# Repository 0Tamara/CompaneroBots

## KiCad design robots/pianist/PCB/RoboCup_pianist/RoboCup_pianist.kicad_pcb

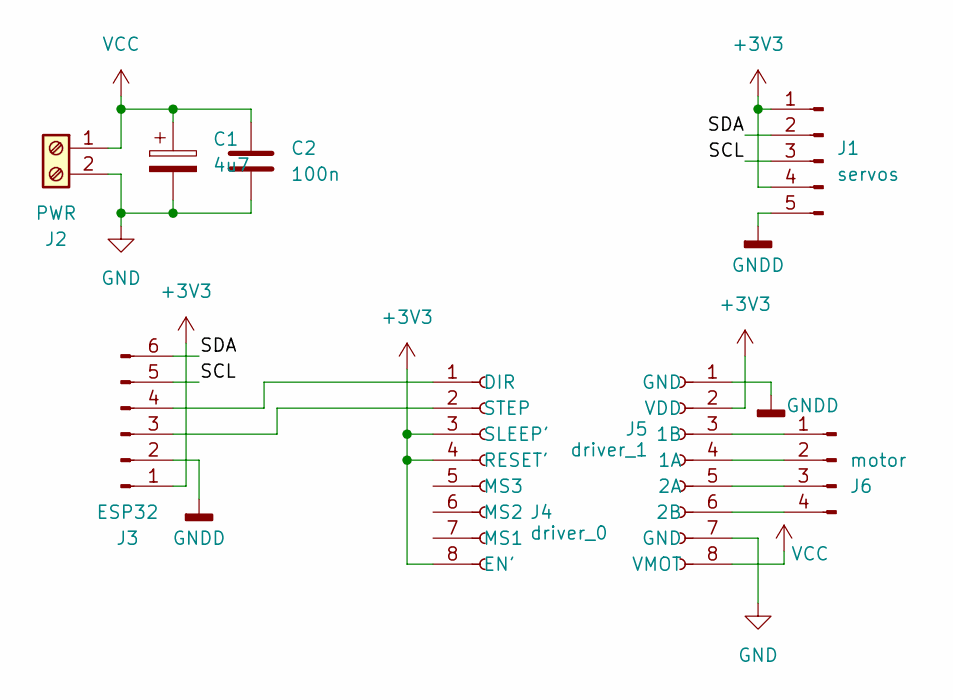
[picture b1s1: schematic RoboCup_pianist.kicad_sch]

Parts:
C1: 4u7; CP_Radial_D5.0mm_P2.50mm
C2: 100n; C_1206_3216Metric_Pad1.33x1.80mm_HandSolder
J1: servos; JST_EH_S5B-EH_1x05_P2.50mm_Horizontal
J2: PWR; TerminalBlock_Xinya_XY308-2.54-2P_1x02_P2.54mm_Horizontal
J3: ESP32; JST_EH_S6B-EH_1x06_P2.50mm_Horizontal
J4: driver_0; PinSocket_1x08_P2.54mm_Vertical
J5: driver_1; PinSocket_1x08_P2.54mm_Vertical
J6: motor; JST_EH_S4B-EH_1x04_P2.50mm_Horizontal

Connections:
+3V3: J1.1, J1.4, J3.1, J4.3 (SLEEP'), J4.4 (RESET'), J4.8 (EN'), J5.2 (VDD)
/SCL: J1.3, J3.5
/SDA: J1.2, J3.6
GND: C1.2, C2.2, J2.2, J5.7 (GND)
GNDD: J1.5, J3.2, J5.1 (GND)
unnamed: J3.3, J4.2 (STEP)
unnamed: J3.4, J4.1 (DIR)
unnamed: J5.4 (1A), J6.2
unnamed: J5.3 (1B), J6.1
unnamed: J5.5 (2A), J6.3
unnamed: J5.6 (2B), J6.4
VCC: C1.1, C2.1, J2.1, J5.8 (VMOT)

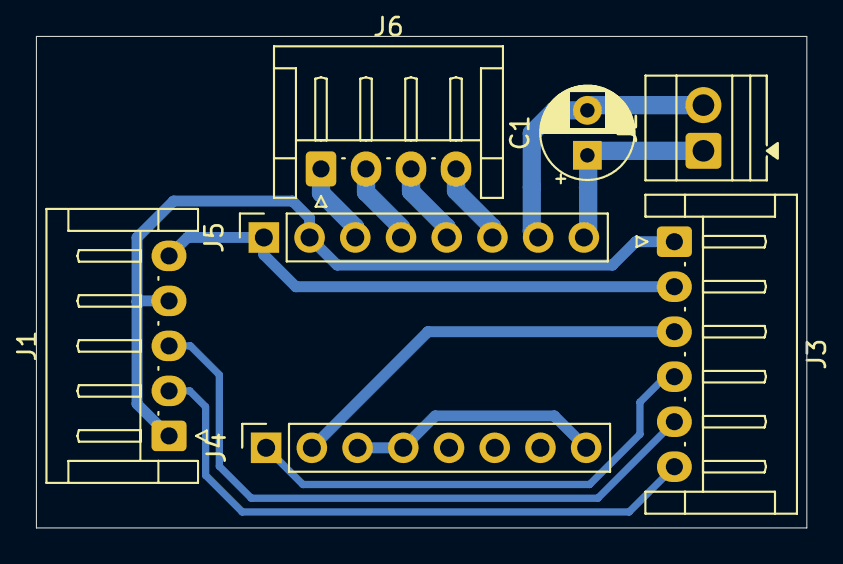
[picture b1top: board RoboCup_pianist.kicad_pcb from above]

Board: 2 copper layers, 42.8 x 27.3 mm, 8 parts (1 on the bottom side), 12 nets.

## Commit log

2025-02-21 folders
2025-02-21 kolesa
2025-02-22 cela choreografia
2025-02-23 inventura
2025-02-23 Emin kod
2025-02-23 uploading files
    kód pre bubeníka + testovacie pre LEDky a servá
2025-02-23 conductor-drummer for song freedom
2025-02-23 tidy work_plan and add details to drummer
2025-02-24 both songs working with drummer
2025-02-24 conductor finito, but not tested
2025-02-24 24.02. vecer
2025-02-25 first run
2025-02-25 first part working
2025-02-25 conductor-drummer-music working
2025-02-25 pianist working
2025-02-25 uhly nastavene
    veronikin kod
2025-02-25 Add files via upload
    klavirista vsetko aj s komunikaciou
2025-02-25 Add files via upload
    toto je na spustenie hudby na PC, treba doinstalovat bleak - do terminalu:
    pip install bleak
2025-02-25 dancer w/ bluetooth
2025-02-25 toto je pre blikanie lediek na klaviristu
2025-02-25 tidy folders
2025-02-26 tanecnik viac do predu
2025-02-26 ledky pre klaviristu
2025-02-26 ledky pre bubenika
2025-02-26 conductor_aux
2025-02-26 LEDs before music
2025-02-26 drummer leds during music
2025-02-26 pianist leds during music
2025-02-26 curtains
2025-02-26 dancer with bluetooth
2025-02-26 ledky
2025-02-26 drummer ledky full
2025-02-27 pianist leds
2025-02-27 jygigkuj
2025-03-28 pdfs
2025-03-28 4 features
2025-04-20 Create camera.py
    zatial iba ten kustik, prerabam cele , musim to dajak zabezpecit bo take onicom
2025-04-20 Update camera.py
    zmenila som to na farby a dalej bude detekovat znaky pre urciteho robota
2025-05-11 zaklad
2025-05-11 pokus_c_ESP32.ino
2025-05-11 3D_models
2025-05-12 update zaklad
2025-05-12 prava_ruka_updated
2025-05-13 Update pokus millis
2025-05-13 prava_r_alg
2025-05-14 update_counter
2025-05-14 c_cpp_properties
2025-05-15 esp-now_example
2025-05-17 data
2025-05-22 zakladna hudbicka + pridanie vecej skladieb
2025-05-22 aby mi nehadzalo vscode errory
2025-05-22 potrbujem kniznicu na serva
2025-05-22 debugging
2025-05-23 init
2025-05-23 another one
2025-05-23 more melody
2025-05-24 finances
2025-05-26 universal
2025-05-27 daco nove tu je
2025-05-28 dancer head 3d models
2025-05-31 dokumentacia
2025-05-31 final
2025-06-02 spolu
2025-06-02 osobitne
2025-06-04 organization
2025-06-05 with accelStepper for motor control
2025-06-05 riadenie krokoveho motore pomocu AccelStepper
2025-06-06 test cez arduino IDE kompilator, bez chyby bezi
2025-06-07 drummer_HW_working
2025-06-07 Revert "drummer_HW_working"
    This reverts commit fe3a571c54342204ccf31f23c1dc99ffba737764.
2025-06-07 Reapply "drummer_HW_working"
    This reverts commit 4890d508c08d32d8f6b2bdf0c0d3db7b30490159.
2025-06-07 vypocet
2025-06-08 esp-now
2025-06-08 curtains_pulleys
2025-06-08 drummer_LEDs_not_working
2025-06-08 novy kod
2025-06-09 gcode
2025-06-09 head_main_gcode
2025-06-09 drummer_2nd_core_working
2025-06-10 ta saak dajak vygenerovane, dajak upravene
2025-06-12 models
2025-06-14 trying_LEDs
    not working with more than 3 LED strips
2025-06-14 LEDs_working
    neopixel libraries
2025-06-14 LEDs working perfectly
    library FastLED
2025-06-15 delete_lego_pianist
2025-06-15 kalibracia_not_working
2025-06-16 kalibracia.ino_compiled
2025-06-16 universal_servo_movement
2025-06-16 nepotrebne - mam universal
2025-06-16 pluscargo
2025-06-17 Odkaz pre Gondeka
    Tote .ino súbory musia byť v priečinku s rovnakým názvom aby si to mohol spustiť
2025-06-17 stepper_motors_speed
    speedInUs = 700
    acceleration = 4000
    works well with 8V/250mA
2025-06-17 rebuild_fast_accel_stepper, no_I2C_pinouts
2025-06-19 postupujeme
2025-06-19 PCB v1.0
2025-06-20 stepper_motors_working
    with new driver (1/8step)
2025-06-20 arduino run without compilation errors
2025-06-20 why do 1 commit when you can do 2? - (variable change in code)
2025-06-21 documentation stuff... how did i managed to spend 1,5 hours on making 3 slides?
2025-06-21 improved constants by Tomas in kalibracia.ino
2025-06-22 pianist added to documentation, missing robots: drummer, raspberry pi, stage scennery
2025-06-23 documentation updated: drummer added
2025-06-23 drummer_leds
    having problem with multiple blinking at the same time (during turning off)
2025-06-23 upgraded - I2C 2
2025-06-24 trying_LEDs_on_2_cores
2025-06-24 LEDs_on_2_cores_working
2025-06-24 LEDs_effects_working
2025-06-24 LED effects in main code
2025-06-24 LEDs with music working
2025-06-24 kalibracia.ino updated for I2C servos
2025-06-25 com_drummer->pianist_working
2025-06-25 freedom added - no compilation errors
2025-06-25 drummer_commun_working_all
2025-06-25 nebezpecne_a_neplynulo
2025-06-26 dancer_servos
2025-06-26 pianist for freedom with communication prop. ready
2025-06-26 pianist within the communication, no comp. errors
2025-06-26 dancer_servos_ramp_1servo_at_a_time
2025-06-27 last upgrades, hopefully this code will work as i wish now
2025-06-28 documentation
2025-06-28 kalibracia.ino working
2025-06-30 documentation updated
2025-06-30 testing
2025-06-30 new (reverse code) moving
2025-06-30 presentation updated
2025-07-01 presentattion
2025-07-01 video - not completed
2025-07-03 kill me ples...
2025-07-03 10 hours of coding.. let me sleep
2025-07-04 working
2025-07-04 pianist - not working
2025-07-05 yesterday's updates
2025-07-05 pokus o vlastnu funkciu
2025-07-06 pianist olsava
2025-07-07 pianist_working
2025-07-07 Pianist HW text
2025-07-08 recordings
2025-07-08 drummer tests
2025-07-08 pianist and drummer working
2025-07-08 cam serial communication working
2025-07-09 voices_somehow_still_saved_even_through_notebook_kaput
2025-07-09 drummer_video
2025-07-09 predbezne video, neni hotove, takisto mame znova problem s časom
2025-07-09 3d models
2025-07-10 documentation updated + pianist
2025-07-10 stupnica added
2025-07-10 pianist
2025-07-10 pre dokumentaciu
2025-07-11 3d modely do rezervy
2025-07-11 curtains wireless working
2025-07-11 comm - camera(hard coded) > drummer > pianist -- working
2025-07-12 camera esp
    without feedback
    not tested
2025-07-12 dancer
2025-07-12 camera esp
2025-07-12 Create Zoznam pri baleni
2025-07-12 .* 2
2025-07-15 com camera, dancer, drummer, curtains
    with feedback on starting melodies
    not tested
2025-07-15 print MAC adresses on setup
2025-07-15 MAC addr
2025-07-16 dancer communicating
2025-07-16 dancer ramp funcion working
    for all servos at the same time
2025-07-16 dancer pins
2025-07-16 camera working 100%
2025-07-16 change addresses and pins
2025-07-17 drummer final not tested
2025-07-17 curtains closing
2025-07-17 final 1st performance
2025-07-18 dancer eyes
2025-07-18 just improvements
2025-07-18 dancer final version 1
    without elbows but working perfectly
2025-07-18 tested working all v2
2025-07-19 superteam pianist 1st song
2025-07-19 pianist_superteam
2025-07-20 test
2025-07-20 superteam ToF working
2025-07-20 superteam goal com
2025-07-20 maybe final
2025-07-20 maybe finally working
2025-07-20 not debugged
2025-07-20 drummer
2025-07-29 kjbj
2025-08-31 music for PSK
2025-09-30 organized
2025-10-06 pianist play 1 note not working
2025-10-09 WiFi
2025-10-09 pianist_universal_functions_working
2025-10-11 testing WiFi AP + HTTP
2025-10-12 web dizajn
2025-10-12 black keys
2025-10-12 piansit csv reading tests
2025-10-12 second v
2025-10-12 csv reading working
2025-10-12 csv reading song header info working
2025-10-12 csv reading complete working
2025-10-12 playing from csv complete working
2025-10-12 all together not completed
2025-10-13 http note playing working
2025-10-14 expo usable
    web site control working
    havasi freedom working
    missing:
    more songs
    better servo pressing values
    web site design perks
2025-10-15 servo calibration system
2025-10-15 songs info feedback in progress
2025-10-15 songs info loading not tested
2025-10-15 pirati z karibiku not tested
2025-10-16 final_not_perfect
2025-10-23 drummer_csv_reading
    problem with timing
2025-10-25 LEDs working
2025-10-25 pianist - drummer com not working
2025-10-25 pianist - drummer com not working
    big problem:
    combining WiFi AP & esp-now on pianist
    timing problems
2025-10-26 async server + esp-now - not working -> give up
2025-10-26 Revert "async server + esp-now - not working -> give up"
    This reverts commit 4d6b11a4c53cb0cc5a5a65b3b3474312a609a477.
2025-10-26 Revert "pianist - drummer com not working"
    This reverts commit ea19d75233a994dcb5e96eeb2a0d6427f8e5146e.
2025-10-26 Revert "pianist - drummer com not working"
    This reverts commit c61ca49fbad8fe7d0aa5cf1e6c6d8ef646f115cb.
2025-10-26 new codes not done
2025-10-26 async server without websocket working
2025-10-26 Uspesne som dostal data cez caly tobogan
2025-10-26 exhibition final - working-ish
2025-10-27 pianist finger calibration
2025-10-27 exhibiton final
    pianist working
    drummer hard coded
2025-11-06 drummer with website working-ish
2025-11-08 drummer website working
2025-11-08 more songs
2025-11-11 final countdown
2026-06-06 old_code_calibration
